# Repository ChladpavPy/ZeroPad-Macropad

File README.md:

# ZeroPad - Custom Macropad

The pathfinder project is great hardware introduction project, but I wanted to do bit more, that I would use daily - specifically for quick shortcuts as a keyboard to my computer.

I designed a custom PCB in KiCad featuring a 2x3 matrix with 6 mechanical Cherry MX switches, and I also added a 4-pin header for a 0.91 I2C OLED display. The display is intended to show the currently active macro profile (such as gaming Mode or work Mode). The board layout was carefully optimized for standard 1U keycap spacing to avoid keycaps collisions.

## Project Features

* **Microcontroller:** Seeed Studio XIAO RP2040
* **Switches:** 6x Mechanical Cherry MX Switches
* **Display:** 0.91 I2C OLED Display for active mode rendering
* **Status LEDs:** 3x basic LEDs for hardware debugging/status
* **PCB Design:** Custom 2-layer board routed in KiCad with dual Cu GND pours for a clean finish.

## Gallery

### Build Preview

### 3D Assembly Renders

### 3D PCB Renders

### PCB Routing & Schematic

---

## Bill of Materials (BOM)

| Component | Qty | Purpose / Description | Price (USD) | Link / Distributor |
| :--- | :---: | :--- | :--- | :--- |
| **Custom PCB Manufacture** | 5 | The actual circuit board to solder everything on. Ordered via JLCPCB standard 2-layer service. | ~$4.74 | [JLCPCB](https://jlcpcb.com) |
| **Seeed Studio XIAO RP2040** | 1 | Main microcontroller / brain for the macropad. Small footprint, plenty of GPIOs. | ~$7.88 | [AliExpress](https://a.aliexpress.com/_EyHIJs2) |
| **0.96" I2C OLED Display** | 1 | Screen to show active macro profiles and current modes. | ~$2.00 | [AliExpress](https://a.aliexpress.com/_EGSrJ7g) |
| **Cherry MX Switches (10-pack)** | 1 | Mechanical switches for the macro buttons. | ~$6.08 | [AliExpress](https://a.aliexpress.com/_EuLENRY) |
| **1U Blank Keycaps (10-pack)** | 1 | Standard covers for the mechanical switches. | ~$3.35 | [AliExpress](https://a.aliexpress.com/_Eyx6JJo) |
| **5mm Green LEDs** | 3 | Status LEDs for debugging (Bought locally, link is equivalent). | ~$0.50 | [SparkFun](https://www.sparkfun.com/products/9592) |
| **330 Ohm Resistors** | 3 | Current limiting resistors for the LEDs (Bought locally). | ~$0.50 | [SparkFun](https://www.sparkfun.com/resistor-330-ohm-1-6th-watt-pth.html) |
| **4.7k Ohm Resistors** | 2 | I2C pull-up resistors for stable OLED communication. | ~$0.50 | [Dratek.cz](https://dratek.cz/arduino-platforma/174921-metalizovany-rezistor-4k7-5w-1.html) |

---

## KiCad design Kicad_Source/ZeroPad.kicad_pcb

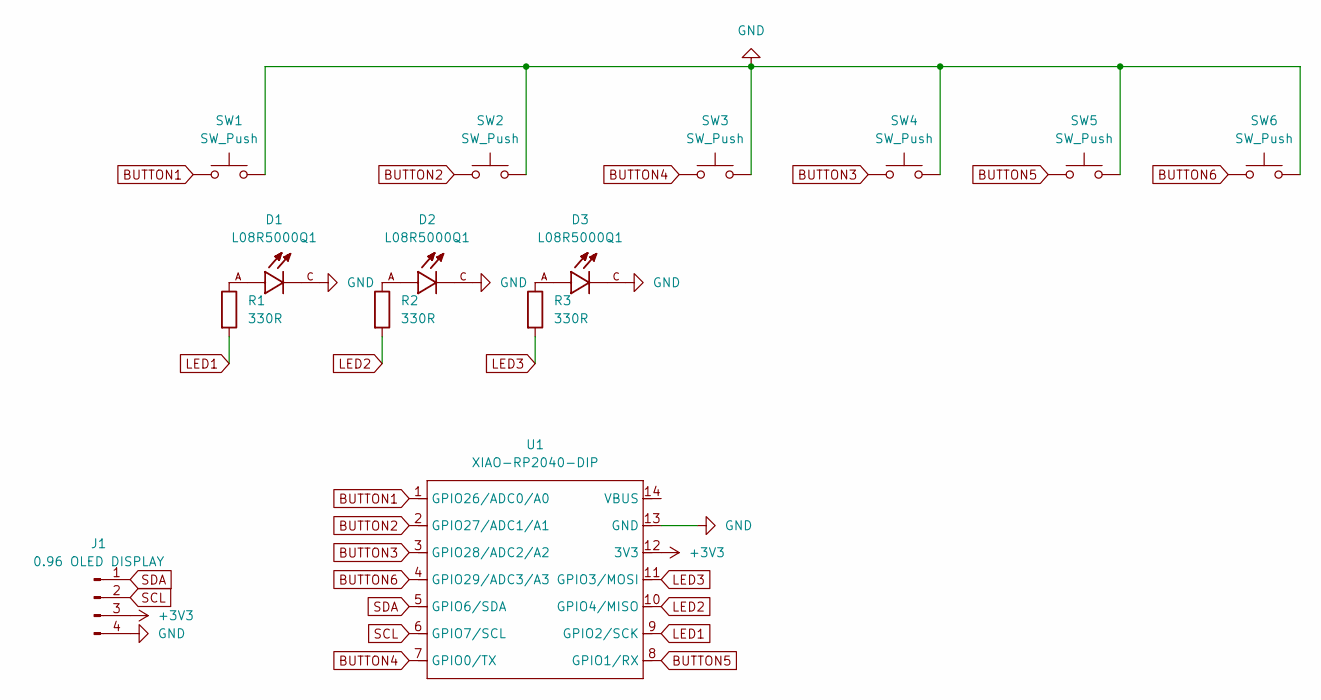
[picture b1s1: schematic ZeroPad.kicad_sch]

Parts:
D1, D2, D3: L08R5000Q1; LEDRD254W57D500H1070; PARTREV NA
J1: 0.96 OLED DISPLAY; PinHeader_1x04_P2.54mm_Vertical
R1, R2, R3: 330R; R_Axial_DIN0204_L3.6mm_D1.6mm_P5.08mm_Horizontal
SW1, SW2, SW3, SW4, SW5, SW6: SW_Push; SW_Cherry_MX_1.00u_PCB
U1: XIAO-RP2040-DIP; XIAO-RP2040-DIP (1)

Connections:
+3V3: J1.3, U1.12 (3V3); also elsewhere on the board
BUTTON1: SW1.1, U1.1 (GPIO26/ADC0/A0)
BUTTON2: SW2.1, U1.2 (GPIO27/ADC1/A1)
BUTTON3: SW4.1, U1.3 (GPIO28/ADC2/A2)
BUTTON4: SW3.1, U1.7 (GPIO0/TX)
BUTTON5: SW5.1, U1.8 (GPIO1/RX)
BUTTON6: SW6.1, U1.4 (GPIO29/ADC3/A3)
GND: D1.C, D2.C, D3.C, J1.4, SW1.2, SW2.2, SW3.2, SW4.2, SW5.2, SW6.2, U1.13 (GND)
LED1: R1.2, U1.9 (GPIO2/SCK)
LED2: R2.2, U1.10 (GPIO4/MISO)
LED3: R3.2, U1.11 (GPIO3/MOSI)
unnamed: D1.A, R1.1
unnamed: D2.A, R2.1
unnamed: D3.A, R3.1
SCL: J1.2, U1.6 (GPIO7/SCL); also elsewhere on the board
SDA: J1.1, U1.5 (GPIO6/SDA); also elsewhere on the board

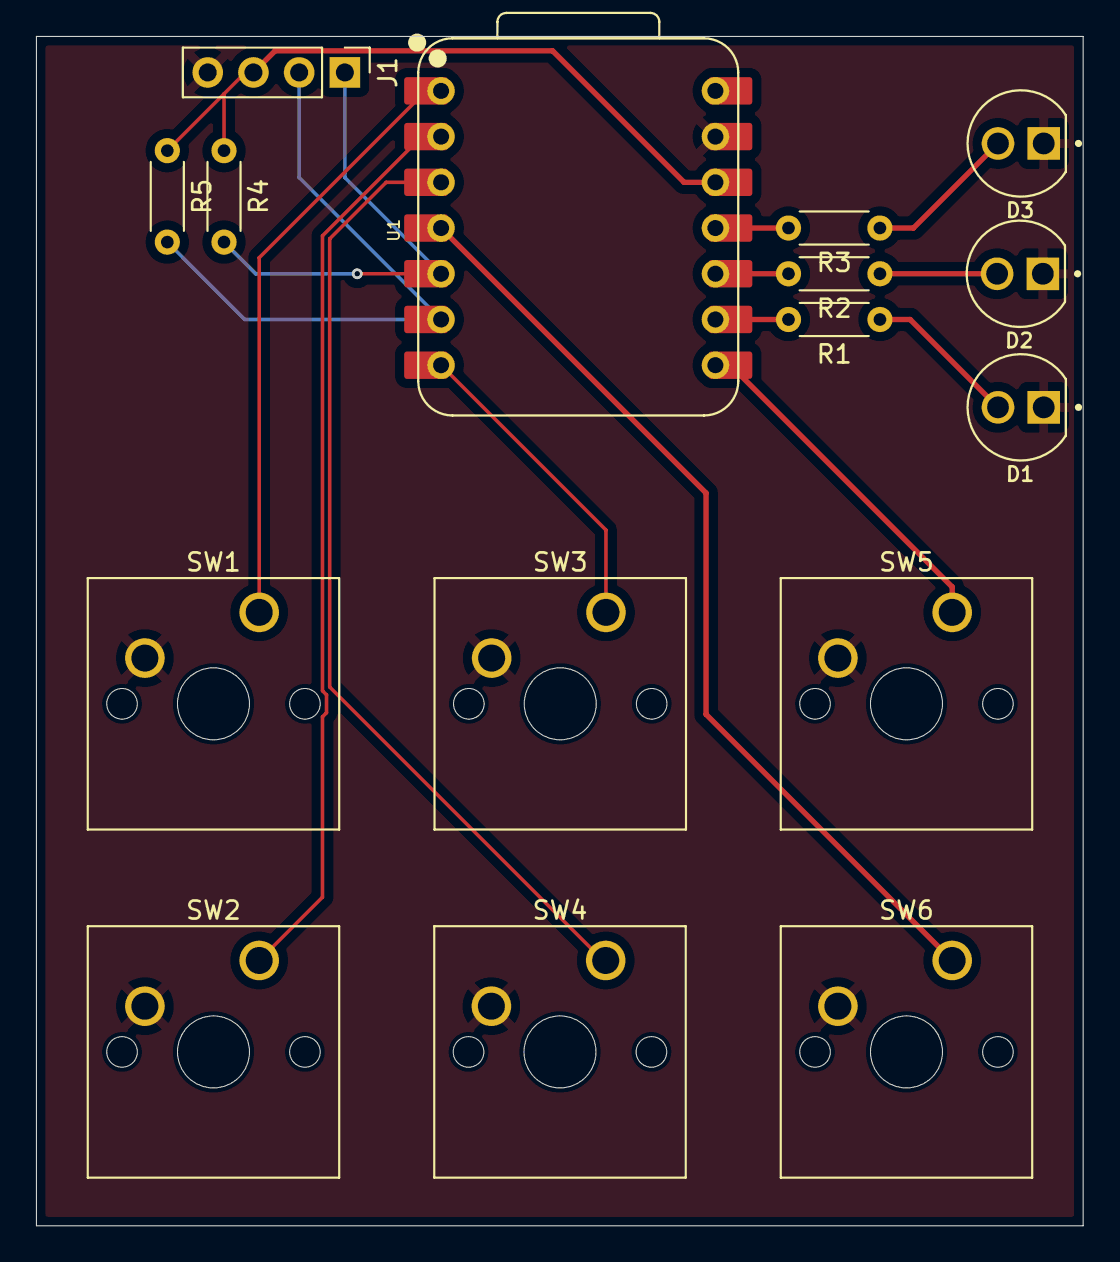
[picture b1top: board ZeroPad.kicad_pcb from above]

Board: 2 copper layers, 58.1 x 66.1 mm, 16 parts (0 on the bottom side), 16 nets.

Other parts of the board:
R4, R5: 4.7K; R_Axial_DIN0204_L3.6mm_D1.6mm_P5.08mm_Horizontal

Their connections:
+3V3: R4.1, R5.1; also elsewhere on the board
SCL: R5.2; also elsewhere on the board
SDA: R4.2; also elsewhere on the board

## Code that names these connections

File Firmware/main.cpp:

#include <Arduino.h>
#include <Wire.h>
#include <Adafruit_GFX.h>
#include <Adafruit_SSD1306.h>
#include <Keyboard.h>

#define MY_SDA 6
#define MY_SCL 7

#define B1 26
#define B2 27
#define B3 28
#define B4 0
#define B5 1
#define B6 29

#define LED1 2
#define LED2 4
#define LED3 3

Adafruit_SSD1306 display(128, 64, &Wire, -1);
bool displayOK = false;

int currentMode = 0;
int menuIndex = 0;
const char* menuLabels[] = {"> Shortcuts", "> Morse code", "> Generator"};

String morseBuffer = "";
String textBuffer = "";
const char* morseTable[] = {
  ".-","-...","-.-.","-..",".","..-.","--.","....","..",
  ".---","-.-",".-..","--","-.","---",".--.","--.-",".-.",
  "...","-","..-","...-",".--","-..-","-.--","--.."
};

int passLen = 13;
String currentPass = "QJA2mep%TrWwJ";
char charset[] = "abcdefghijklmnopqrstuvwxyzABCDEFGHIJKLMNOPQRSTUVWXYZ0123456789!@#$%^&*";

void setup() {
  pinMode(LED1, OUTPUT);
  pinMode(LED2, OUTPUT);
  pinMode(LED3, OUTPUT);
  
  pinMode(B1, INPUT_PULLUP);
  pinMode(B2, INPUT_PULLUP);
  pinMode(B3, INPUT_PULLUP);
  pinMode(B4, INPUT_PULLUP);
  pinMode(B5, INPUT_PULLUP);
  pinMode(B6, INPUT_PULLUP);

  pinMode(MY_SDA, INPUT_PULLUP);
  pinMode(MY_SCL, INPUT_PULLUP);
  delay(10);
  
  Wire.setSDA(MY_SDA);
  Wire.setSCL(MY_SCL);
  Wire.setClock(100000);
  Wire.begin();

  if (display.begin(SSD1306_SWITCHCAPVCC, 0x3C) || display.begin(SSD1306_SWITCHCAPVCC, 0x3D)) {
    displayOK = true;
  }
  
  Keyboard.begin();
  randomSeed(analogRead(26));
  delay(1000);
  drawMenu();
}

void loop() {
  if (currentMode == 0) {
    if (digitalRead(B1) == LOW) { menuIndex--; if(menuIndex < 0) menuIndex = 2; drawMenu(); delay(200); }
    if (digitalRead(B2) == LOW) { menuIndex++; if(menuIndex > 2) menuIndex = 0; drawMenu(); delay(200); }
    if (digitalRead(B3) == LOW) { currentMode = menuIndex + 1; drawMode(); delay(200); }
  } 
  else if (currentMode == 1) {
    if (digitalRead(B6) == LOW) { currentMode = 0; drawMenu(); delay(200); }
    if (digitalRead(B1) == LOW) { Keyboard.press(KEY_SCAN_PREVIOUS); Keyboard.releaseAll(); delay(200); }
    if (digitalRead(B2) == LOW) { Keyboard.press(KEY_PLAY_PAUSE); Keyboard.releaseAll(); delay(200); }
    if (digitalRead(B5) == LOW) { Keyboard.press(KEY_LEFT_GUI); Keyboard.press(KEY_LEFT_SHIFT); Keyboard.press('s'); Keyboard.releaseAll(); delay(200); }
  } 
  else if (currentMode == 2) {
    if (digitalRead(B6) == LOW) { currentMode = 0; drawMenu(); delay(200); }
    if (digitalRead(B1) == LOW) { morseBuffer += "."; drawMorse(); delay(200); }
    if (digitalRead(B2) == LOW) { morseBuffer += "-"; drawMorse(); delay(200); }
    if (digitalRead(B3) == LOW) {
      for (int i = 0; i < 26; i++) {
        if (morseBuffer == morseTable[i]) {
          textBuffer += (char)('A' + i);
          Keyboard.print((char)('a' + i));
          break;
        }
      }
      morseBuffer = "";
      drawMorse();
      delay(200);
    }
    if (digitalRead(B4) == LOW) { morseBuffer = ""; drawMorse(); delay(200); }
    if (digitalRead(B5) == LOW) { textBuffer += " "; Keyboard.print(" "); drawMorse(); delay(200); }
  } 
  else if (currentMode == 3) {
    if (digitalRead(B6) == LOW) { currentMode = 0; drawMenu(); delay(200); }
    if (digitalRead(B1) == LOW) { passLen++; if(passLen > 25) passLen = 25; drawGenerator(); delay(200); }
    if (digitalRead(B2) == LOW) { passLen--; if(passLen < 4) passLen = 4; drawGenerator(); delay(200); }
    if (digitalRead(B3) == LOW) { 
      currentPass = "";
      for(int i=0; i<passLen; i++) {
        currentPass += charset[random(0, strlen(charset))];
      }
      drawGenerator(); 
      delay(200); 
    }
    if (digitalRead(B4) == LOW) { Keyboard.print(currentPass); delay(200); }
  }
}

void drawMenu() {
  if(!displayOK) return;
  display.clearDisplay();
  display.setTextColor(SSD1306_WHITE);
  display.setTextSize(1);
  display.setCursor(0,0);
  display.println("ZEROPAD OS");
  display.println("----------------");
  for(int i = 0; i < 3; i++) {
    if(i == menuIndex) {
      display.print("-> ");
    } else {
      display.print("   ");
    }
    display.println(menuLabels[i]);
  }
  display.display();
}

void drawMode() {
  if(currentMode == 1) drawShortcuts();
  if(currentMode == 2) drawMorse();
  if(currentMode == 3) drawGenerator();
}

void drawShortcuts() {
  if(!displayOK) return;
  display.clearDisplay();
  display.setCursor(0,0);
  display.println("SHORTCUTS");
  display.println("----------------");
  display.println("B1: Prev Track");
  display.println("B2: Play/Pause");
  display.println("B5: Win+Shift+S");
  display.println("B6: Zpet do Menu");
  display.display();
}

void drawMorse() {
  if(!displayOK) return;
  display.clearDisplay();
  display.setCursor(0,0);
  display.println("MORSE CODE");
  display.println("----------------");
  display.print("Znak: "); 
  display.println(morseBuffer);
  display.print("Text: "); 
  display.println(textBuffer);
  display.display();
}

void drawGenerator() {
  if(!displayOK) return;
  display.clearDisplay();
  display.setCursor(0,0);
  display.println("[ GENERATOR ]");
  display.print("Delka: ");
  display.println(passLen);
  display.println("Heslo:");
  display.println(currentPass);
  display.setCursor(0, 56);
  display.println("B1:len+ B2:len- B3:Gen");
  display.display();
}

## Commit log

2026-05-23 Revise README with project overview and specifications
    Expanded project details, features, and BOM in README.
2026-05-23 Remove firmware note from README
    Removed firmware note about the project and OLED display.
2026-06-01 Add 3D assembly renders to README
    Added 3D assembly renders to the gallery section.
2026-06-01 Fix PCB 3D image links in README
    Updated PCB 3D render images in README.
2026-06-01 Replace PCB 3D images with updated versions
    Updated PCB 3D render images in README.
2026-06-08 Revise BOM with new components and descriptions
    Updated BOM.csv to include new components and their details.
2026-06-30 Rename image.png to schematics2.png
2026-06-30 Rename image.png to pcb_new.png
2026-06-30 Rename image.png to pcb_new2.png
